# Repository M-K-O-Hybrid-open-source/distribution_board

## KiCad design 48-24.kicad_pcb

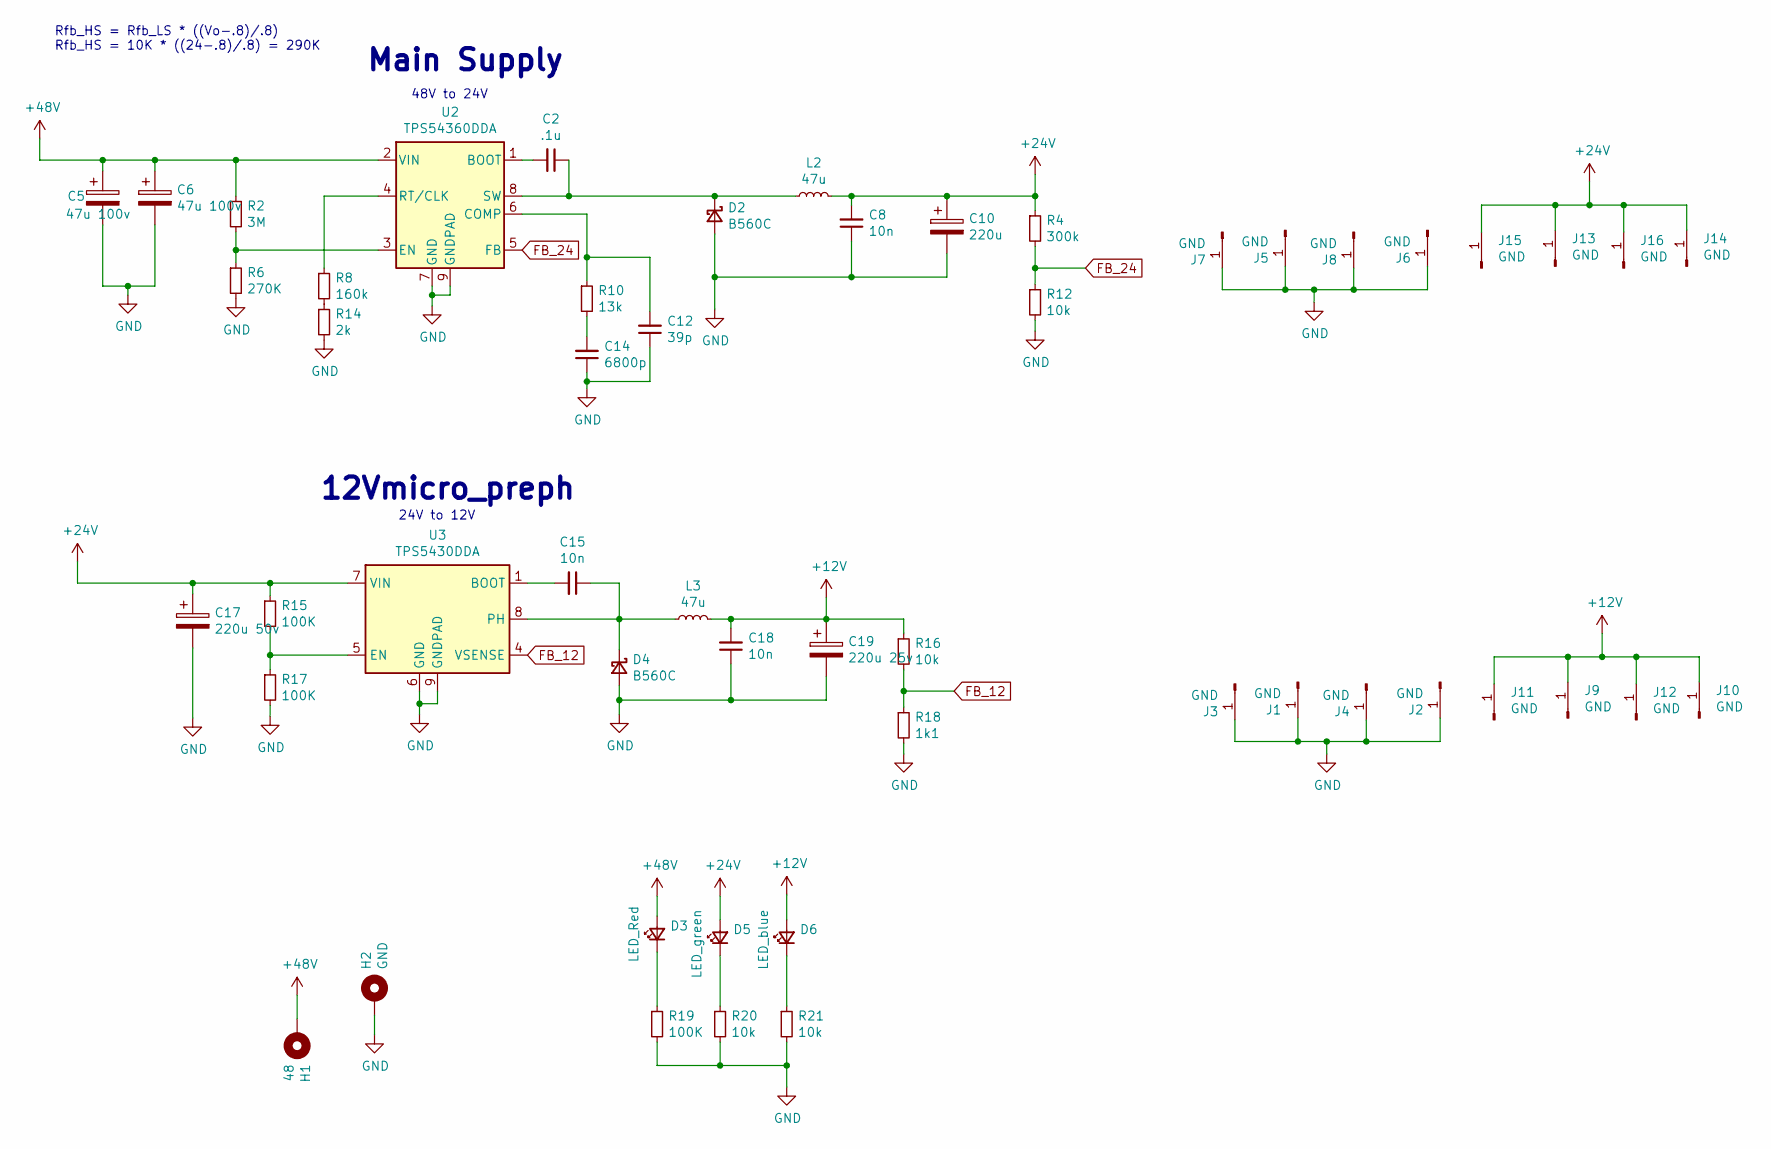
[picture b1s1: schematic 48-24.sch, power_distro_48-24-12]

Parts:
C2: .1u; C_0805_2012Metric
C5, C6: 47u 100v; CP_Elec_10x10
C8: 10n; C_1206_3216Metric_Pad1.42x1.75mm_HandSolder
C10: 220u; CP_Elec_10x10
C12: 39p; C_0402_1005Metric
C14: 6800p; C_0402_1005Metric
C15: 10n; C_0805_2012Metric
C17: 220u 50v; CP_Elec_10x10
C18: 10n; C_1206_3216Metric
C19: 220u 25v; CP_Elec_10x10
D2, D4: B560C; D_SMC
D3: LED_Red; LED_0603_1608Metric
D5: LED_green; LED_0805_2012Metric
D6: LED_blue; LED_0805_2012Metric
H1: 48; MountingHole_2.2mm_M2_DIN965_Pad
H2: GND; MountingHole_2.2mm_M2_DIN965_Pad
J1, J2, J3, J4, J5, J6, J7, J8, J9, J10, J11, J12, J13, J14, J15, J16: GND; SolderWirePad_1x01_SMD_1x2mm
L2: 47u; L_12x12mm_H8mm
L3: 47u; L_12x12mm_H6mm
R2: 3M; R_0805_2012Metric
R4: 300k; R_0805_2012Metric
R6: 270K; R_0805_2012Metric
R8: 160k; R_0805_2012Metric
R10: 13k; R_0805_2012Metric
R12, R16, R20, R21: 10k; R_0805_2012Metric
R14: 2k; R_0805_2012Metric
R15, R17, R19: 100K; R_0805_2012Metric
R18: 1k1; R_0805_2012Metric
U2: TPS54360DDA; TI_SO-PowerPAD-8_ThermalVias
U3: TPS5430DDA; TI_SO-PowerPAD-8_ThermalVias

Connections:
+12V: C18.2, C19.1, D6.2 (A), J9.1, J10.1, J11.1, J12.1, L3.2, R16.1
+24V: C8.2, C10.1, C17.1, D5.2 (A), J13.1, J14.1, J15.1, J16.1, L2.2, R4.1, R15.1, U3.7 (VIN)
+48V: C5.1, C6.1, D3.2 (A), H1.1, R2.1, U2.2 (VIN)
FB_12: R16.2, R18.1, U3.4 (VSENSE)
FB_24: R4.2, R12.1, U2.5 (FB)
GND: C5.2, C6.2, C8.1, C10.2, C12.1, C14.1, C17.2, C18.1, C19.2, D2.2 (A), D4.2 (A), H2.1, J1.1, J2.1, J3.1, J4.1, J5.1, J6.1, J7.1, J8.1, R6.2, R12.2, R14.2, R17.2, R18.2, R19.2, R20.2, R21.2, U2.7 (GND), U2.9 (GNDPAD), U3.6 (GND), U3.9 (GNDPAD)
unnamed: C2.1, D2.1 (K), L2.1, U2.8 (SW)
unnamed: C2.2, U2.1 (BOOT)
unnamed: C12.2, R10.1, U2.6 (COMP)
unnamed: C14.2, R10.2
unnamed: C15.1, D4.1 (K), L3.1, U3.8 (PH)
unnamed: C15.2, U3.1 (BOOT)
unnamed: D3.1 (K), R19.1
unnamed: D5.1 (K), R20.1
unnamed: D6.1 (K), R21.1
unnamed: R2.2, R6.1, U2.3 (EN)
unnamed: R8.1, U2.4 (RT/CLK)
unnamed: R8.2, R14.1
unnamed: R15.2, R17.1, U3.5 (EN)

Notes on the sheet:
Rfb_HS = Rfb_LS * ((Vo-.8)/.8) Rfb_HS = 10K * ((24-.8)/.8) = 290K
48V to 24V
24V to 12V
Main Supply
12Vmicro_preph

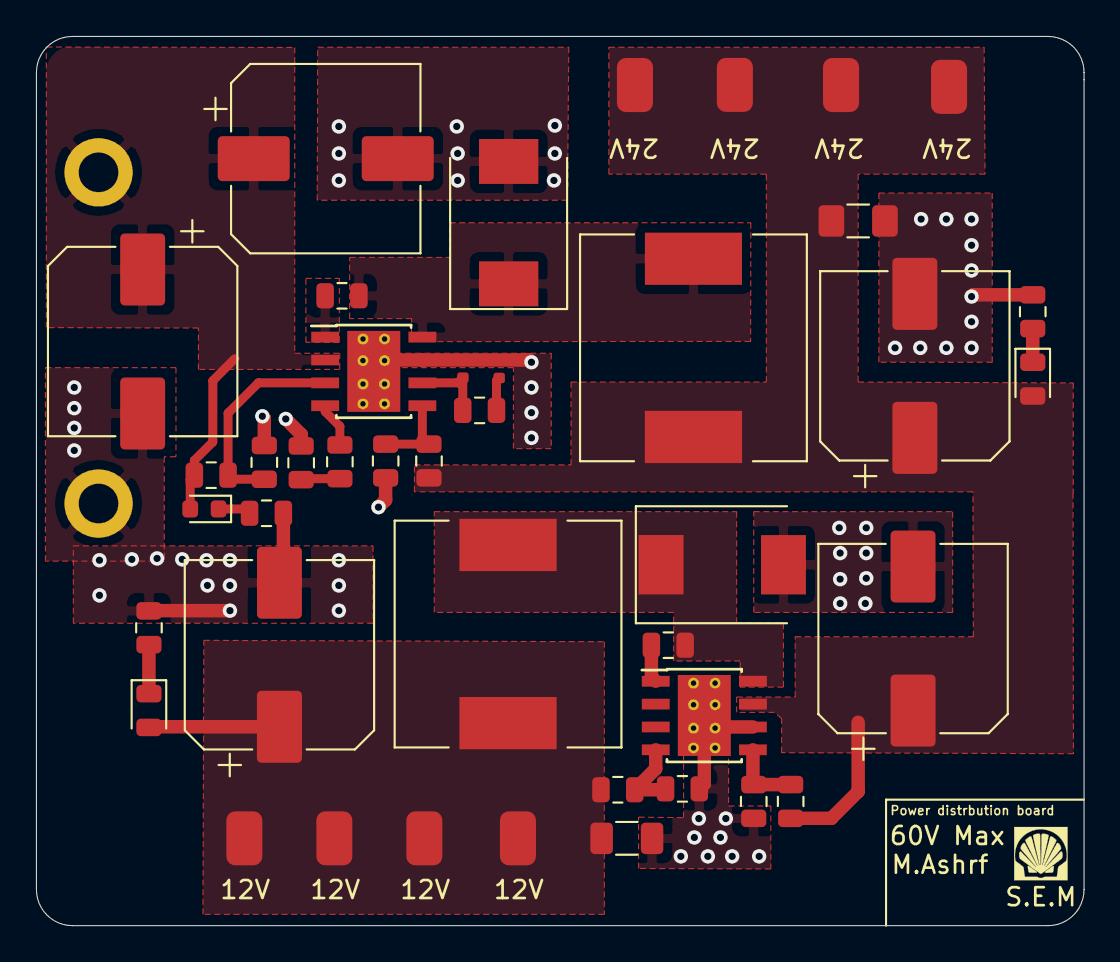
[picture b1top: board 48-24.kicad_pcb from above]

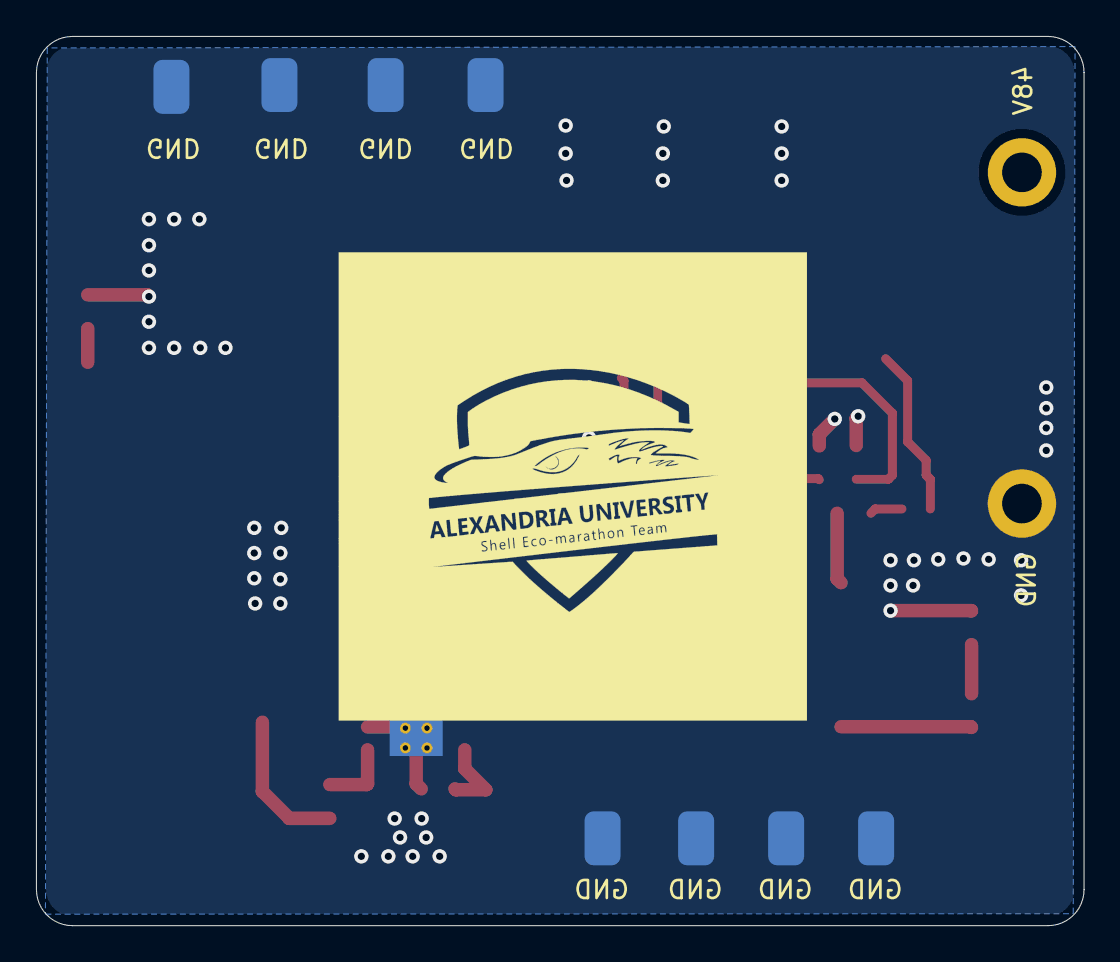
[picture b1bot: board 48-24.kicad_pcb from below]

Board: 2 copper layers, 58.2 x 49.4 mm, 52 parts (8 on the bottom side), 19 nets.
